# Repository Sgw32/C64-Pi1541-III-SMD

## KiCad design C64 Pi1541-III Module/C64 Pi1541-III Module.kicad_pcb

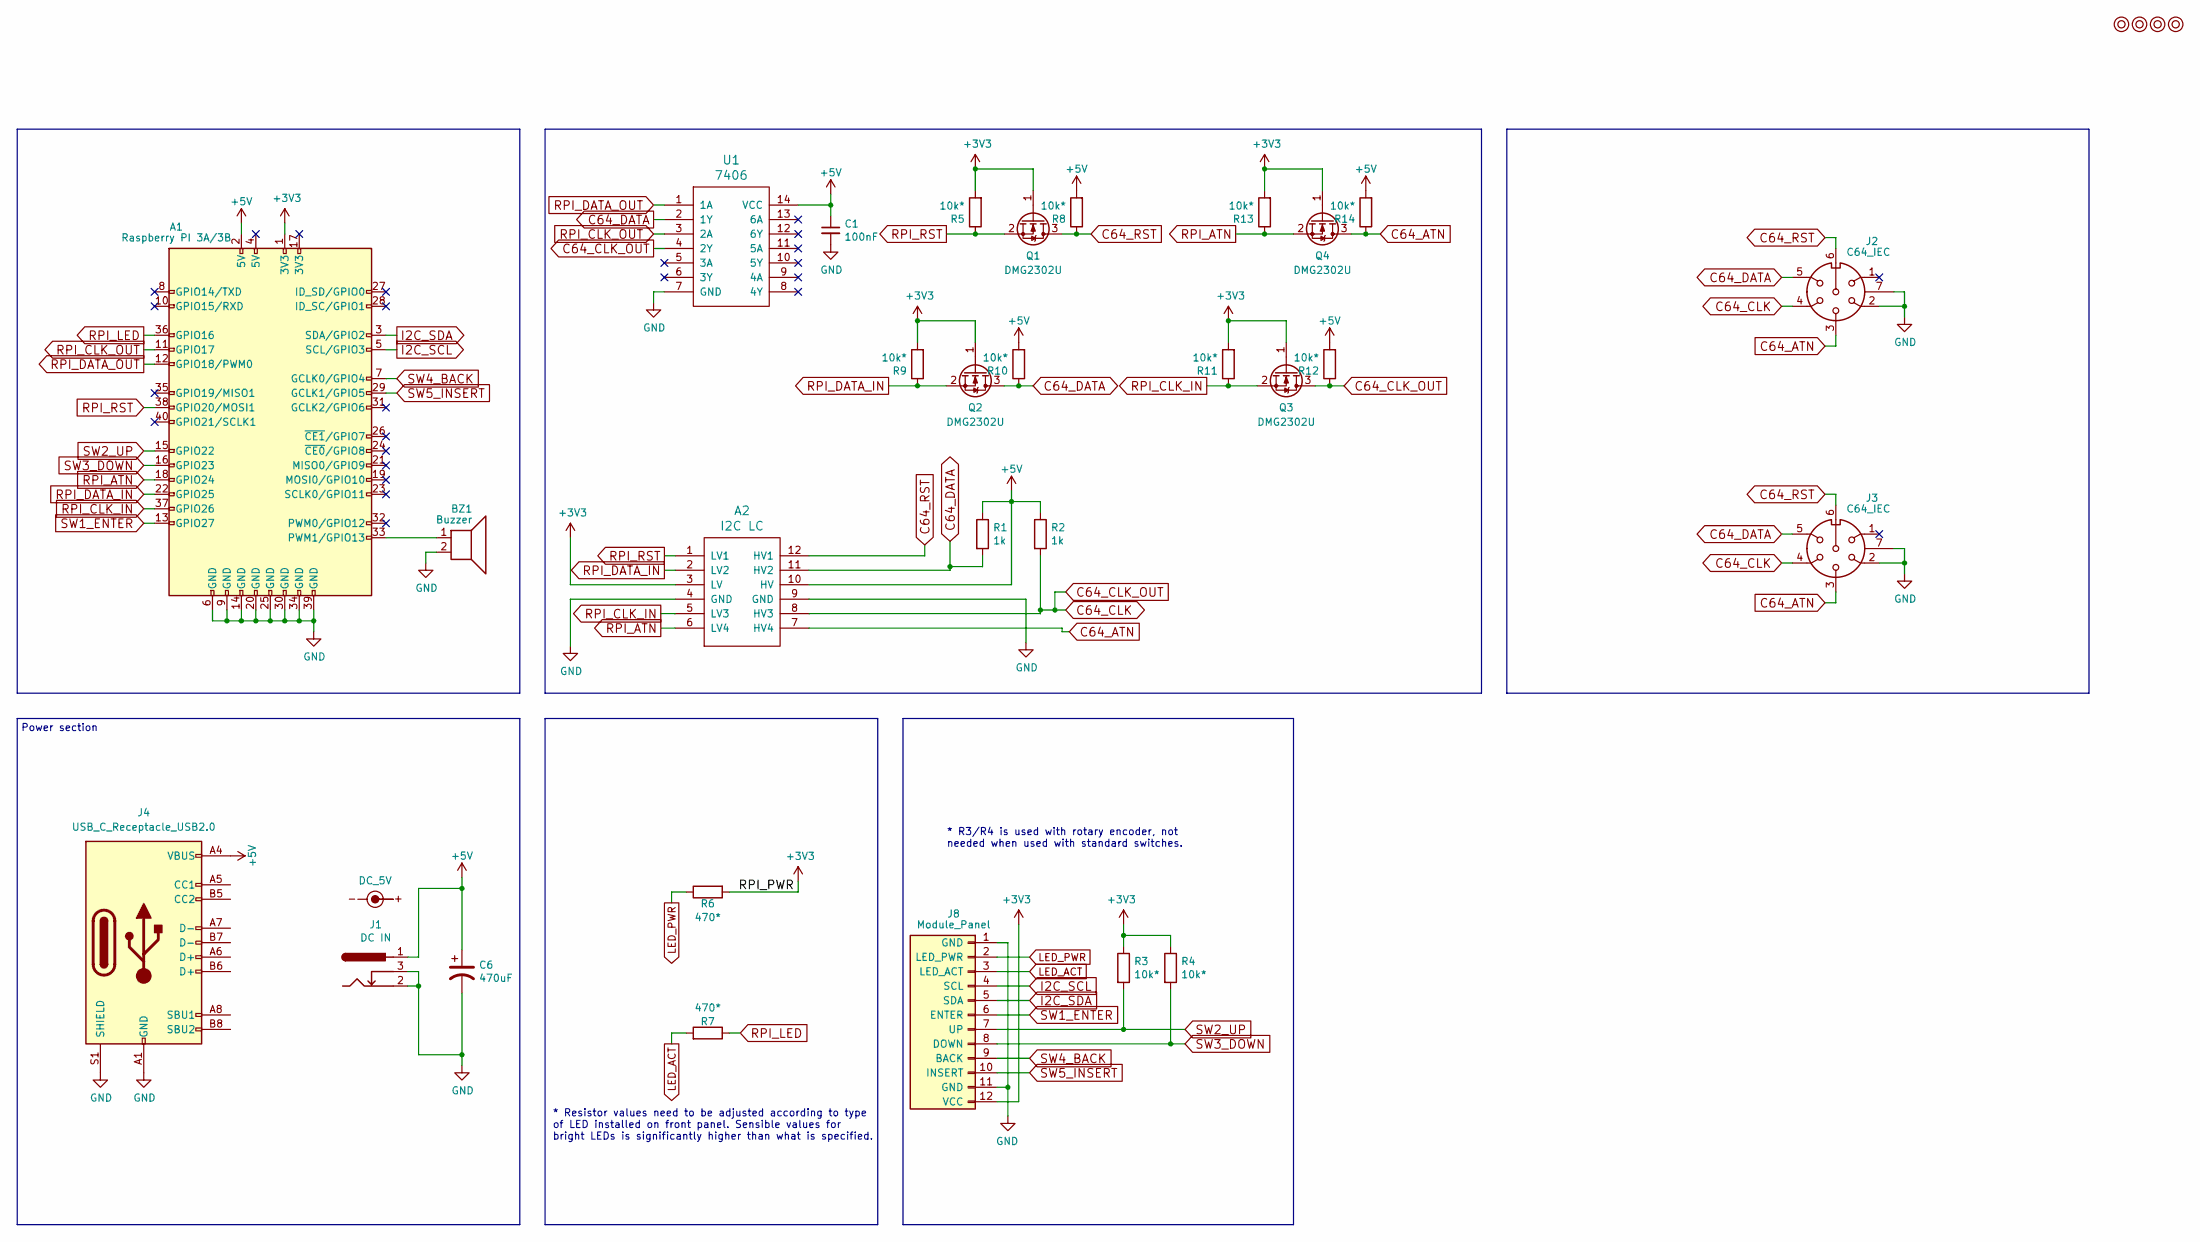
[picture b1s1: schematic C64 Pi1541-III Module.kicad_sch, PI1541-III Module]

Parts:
A1: Raspberry PI 3A/3B; Raspberry_Pi_3B_Socketed_THT_FaceDown_MountingHoles
A2: I2C LC; 4CH_I2C_Level_Converter
BZ1: Buzzer; Buzzer_12x9.5RM7.6
C1: 100nF; C_0805_2012Metric
C6: 470uF; CP_Elec_10x7.7
J1: DC IN; BarrelJack_CLIFF_FC681465S_SMT_Horizontal
J2, J3: C64_IEC; DIN6_IEC
J4: USB_C_Receptacle_USB2.0; USB_C_Receptacle_XKB_U262-16XN-4BVC11
J8: Module_Panel
M1, M2, M3, M4: Mounting; M3
Q1, Q2, Q3, Q4: DMG2302U; SOT-23
R1, R2: 1k; R_0805_2012Metric
R3, R4, R5, R8, R9, R10, R11, R12, R13, R14: 10k*; R_0805_2012Metric
R6, R7: 470*; R_0805_2012Metric
SYM1: DC_5V; PWR_Specification
U1: 7406; SO-14_3.9x8.65mm_P1.27mm

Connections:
+3V3: A1.1 (3V3), A2.3 (LV), J8.12 (VCC), Q1.1 (G), Q2.1 (G), Q3.1 (G), Q4.1 (G), R3.1, R4.1, R5.2, R6.2, R9.2, R11.2, R13.2
+5V: A1.2 (5V), A2.10 (HV), C1.1, C6.1, J1.1, J4.A4 (VBUS), J4.A9 (VBUS), J4.B4 (VBUS), J4.B9 (VBUS), R1.1, R2.1, R8.2, R10.2, R12.2, R14.2, U1.14 (VCC)
C64_ATN: A2.7 (HV4), J2.3, J3.3, Q4.3 (D), R14.1
C64_CLK: A2.8 (HV3), J2.4, J3.4, Q3.3 (D), R2.2, R12.1, U1.4 (2Y)
C64_DATA: A2.11 (HV2), J2.5, J3.5, Q2.3 (D), R1.2, R10.1, U1.2 (1Y)
C64_RST: A2.12 (HV1), J2.6, J3.6, Q1.3 (D), R8.1
GND: A1.6 (GND), A1.9 (GND), A1.14 (GND), A1.20 (GND), A1.25 (GND), A1.30 (GND), A1.34 (GND), A1.39 (GND), A2.4 (GND), A2.9 (GND), BZ1.2, C1.2, C6.2, J1.2, J1.3, J2.2, J2.7, J3.2, J3.7, J4.A1 (GND), J4.A12 (GND), J4.B1 (GND), J4.B12 (GND), J4.S1 (SHIELD), J8.1 (GND), J8.11 (GND), U1.7 (GND)
I2C_SCL: A1.5 (SCL/GPIO3), J8.4 (SCL)
I2C_SDA: A1.3 (SDA/GPIO2), J8.5 (SDA)
LED_ACT: J8.3 (LED_ACT), R7.2
LED_PWR: J8.2 (LED_PWR), R6.1
unnamed: A1.33 (PWM1/GPIO13), BZ1.1
RPI_ATN: A1.18 (GPIO24), A2.6 (LV4), Q4.2 (S), R13.1
RPI_CLK_IN: A1.37 (GPIO26), A2.5 (LV3), Q3.2 (S), R11.1
RPI_CLK_OUT: A1.11 (GPIO17), U1.3 (2A)
RPI_DATA_IN: A1.22 (GPIO25), A2.2 (LV2), Q2.2 (S), R9.1
RPI_DATA_OUT: A1.12 (GPIO18/PWM0), U1.1 (1A)
RPI_LED: A1.36 (GPIO16), R7.1
RPI_RST: A1.38 (GPIO20/MOSI1), A2.1 (LV1), Q1.2 (S), R5.1
SW1_ENTER: A1.13 (GPIO27), J8.6 (ENTER)
SW2_UP: A1.15 (GPIO22), J8.7 (UP), R3.2
SW3_DOWN: A1.16 (GPIO23), J8.8 (DOWN), R4.2
SW4_BACK: A1.7 (GCLK0/GPIO4), J8.9 (BACK)
SW5_INSERT: A1.29 (GCLK1/GPIO5), J8.10 (INSERT)

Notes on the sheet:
Power section
* R3/R4 is used with rotary encoder, not needed when used with standard switches.
* Resistor values need to be adjusted according to type of LED installed on front panel. Sensible values for bright LEDs is significantly higher than what is specified.

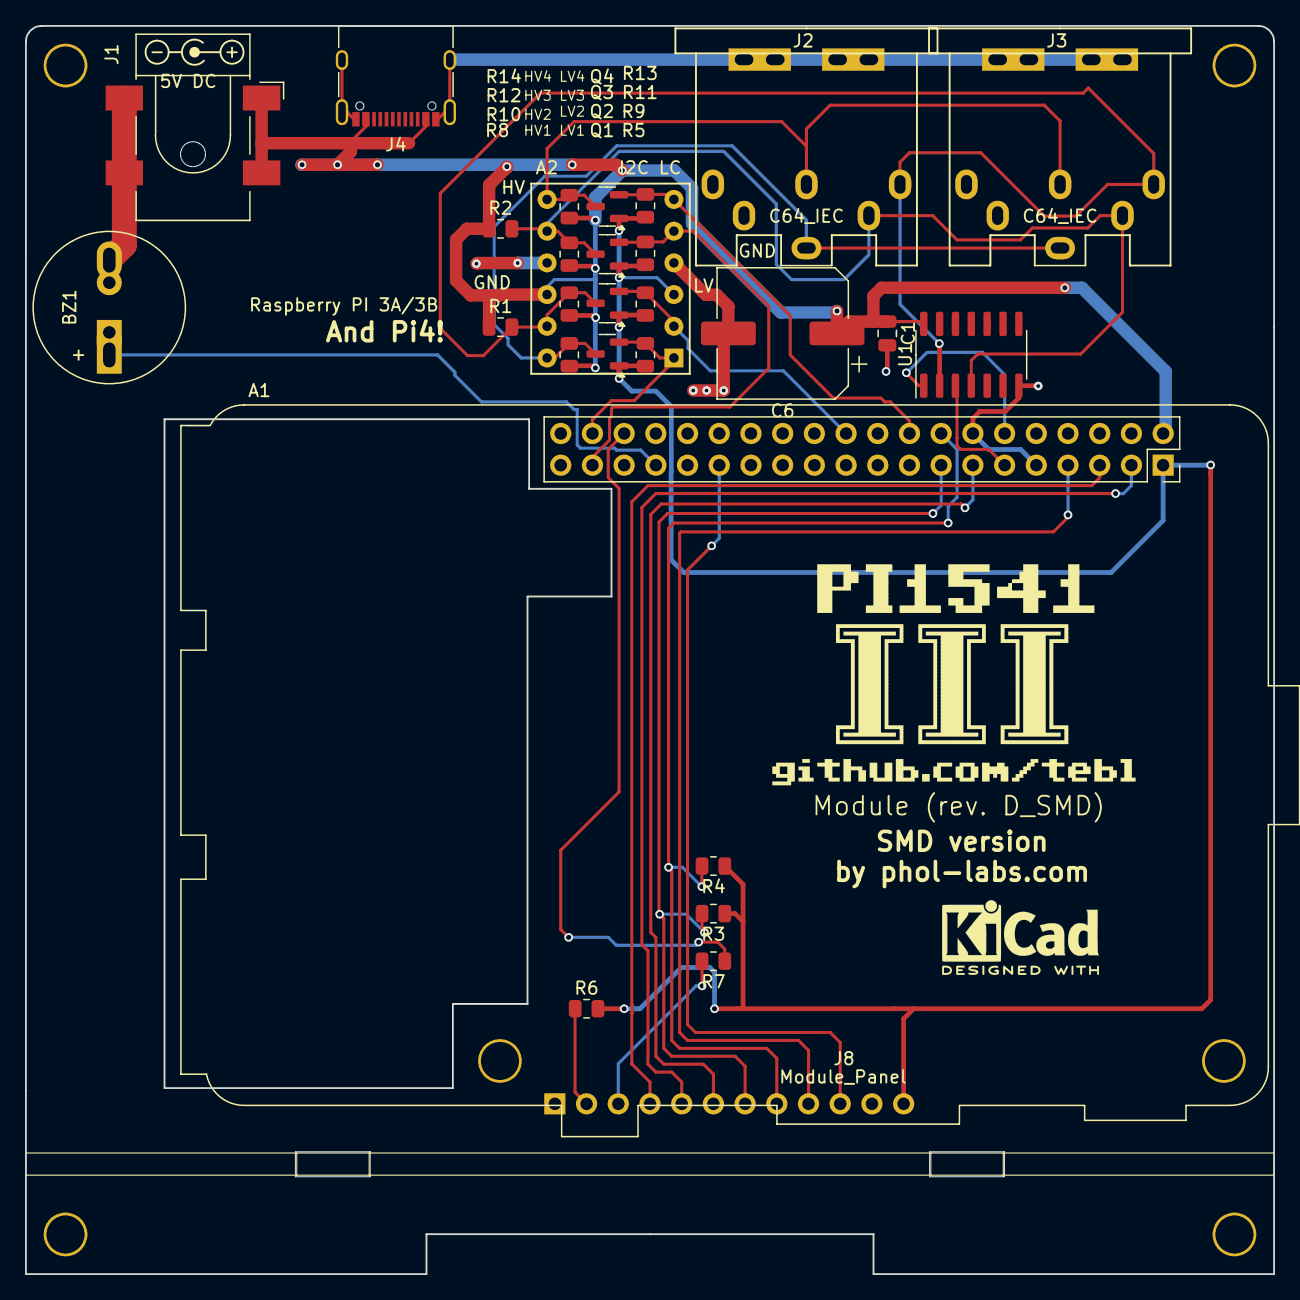
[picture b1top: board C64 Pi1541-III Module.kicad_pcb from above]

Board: 2 copper layers, 100.0 x 100.0 mm, 35 parts (1 on the bottom side), 24 nets.

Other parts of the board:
Pi1541-drive: Pi1541-drive

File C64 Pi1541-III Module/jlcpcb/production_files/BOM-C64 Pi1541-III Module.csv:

Comment,Designator,Footprint,LCSC,Quantity
DC IN,J1,BarrelJack_CLIFF_FC681465S_SMT_Horizontal,C114916,1
Raspberry PI 3A/3B,A1,Raspberry_Pi_3B_Socketed_THT_FaceDown_MountingHoles,C132132,1
USB_C_Receptacle_USB2.0,J4,USB_C_Receptacle_XKB_U262-16XN-4BVC11,C165948,1
10k*,"R10,R11,R12,R13,R14,R3,R4,R5,R8,R9",R_0805_2012Metric,C17414,10
1k,"R1,R2",R_0805_2012Metric,C17513,2
470*,"R6,R7",R_0805_2012Metric,C17710,2
Buzzer,BZ1,Buzzer_12x9.5RM7.6,C252916,1
DMG2302U,"Q1,Q2,Q3,Q4",SOT-23,C427390,4
100nF,C1,C_0805_2012Metric,C49678,1
7406,U1,SO-14_3.9x8.65mm_P1.27mm,C5592,1
470uF,C6,CP_Elec_10x7.7,C88671,1

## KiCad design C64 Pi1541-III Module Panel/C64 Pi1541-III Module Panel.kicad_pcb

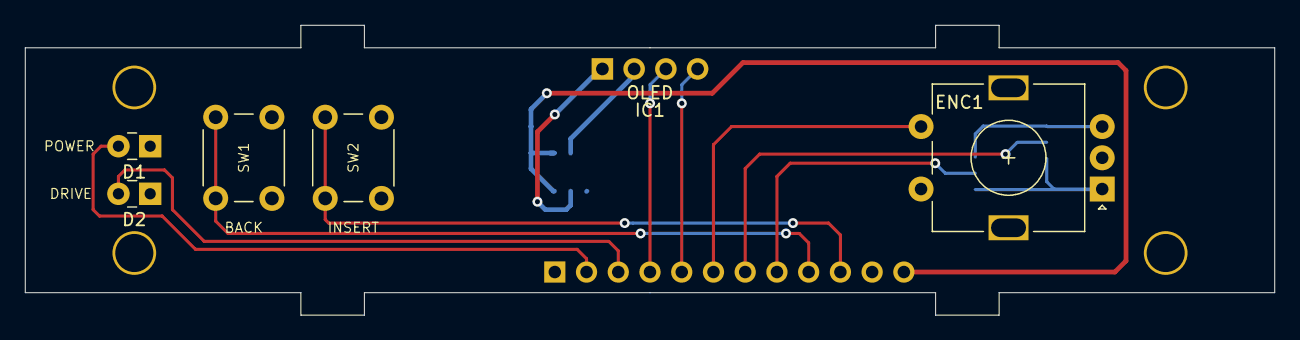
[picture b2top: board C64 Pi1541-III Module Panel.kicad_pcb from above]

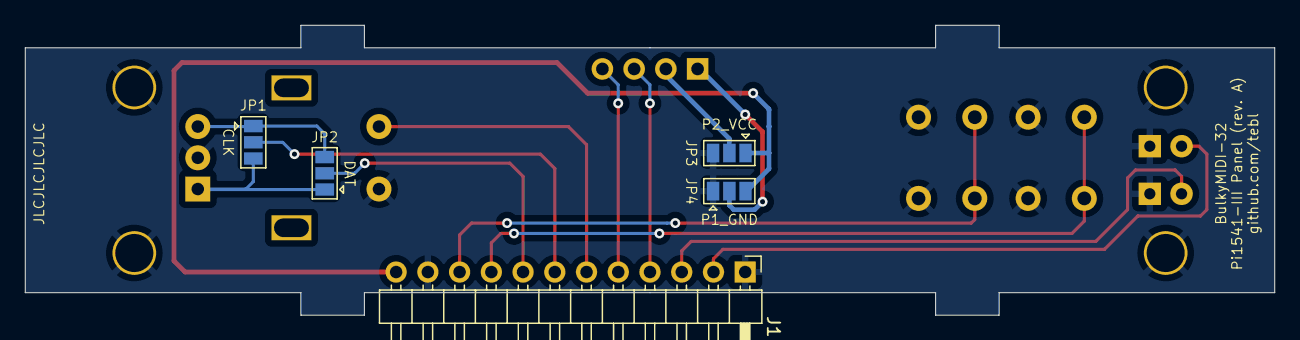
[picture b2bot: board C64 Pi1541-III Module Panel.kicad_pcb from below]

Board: 2 copper layers, 100.0 x 23.2 mm, 15 parts (5 on the bottom side), 15 nets.

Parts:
D1: POWER; LED_Rectangular_W3.0mm_H2.0mm
D2: DRIVE; LED_Rectangular_W3.0mm_H2.0mm
ENC1: Rotary_Encoder_Switch; RotaryEncoder_Alps_EC11E-Switch_Vertical_H20mm
IC1: OLED; 1.3_I2C_OLED_No_mounting
J1: Module Panel; PinHeader_1x12_P2.54mm_Horizontal
JP1: CLK; SolderJumper-3_P1.3mm_Open_Pad1.0x1.5mm
JP2: DAT; SolderJumper-3_P1.3mm_Open_Pad1.0x1.5mm
JP3: P1_GND; SolderJumper-3_P1.3mm_Open_Pad1.0x1.5mm
JP4: P2_VCC; SolderJumper-3_P1.3mm_Open_Pad1.0x1.5mm
M1, M2, M3, M4: Mounting_Pin; M3_pin
SW1: BACK; SW_PUSH_6mm
SW2: INSERT; SW_PUSH_6mm

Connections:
/A: ENC1.A, JP1.3, JP2.1
/B: ENC1.B, JP1.1, JP2.3
GND: D1.1, D2.1, ENC1.C, ENC1.S2, J1.1, J1.11, JP3.1, JP4.3, M1.1, M2.1, M3.1, M4.1, SW1.2, SW2.2
I2C_SCL: IC1.3, J1.4
I2C_SDA: IC1.4, J1.5
LED_ACT: D2.2, J1.3
LED_PWR: D1.2, J1.2
unnamed: IC1.1, JP3.2
unnamed: IC1.2, JP4.2
SW_BACK: J1.9, SW1.1
SW_DOWN: J1.8, JP2.2
SW_ENTER: ENC1.S1, J1.6
SW_INSERT: J1.10, SW2.1
SW_UP: J1.7, JP1.2
VCC: J1.12, JP3.3, JP4.1

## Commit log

2025-03-15 SMD option for Pi1541-III
2025-07-16 Version with more SMD comp - finished, there will be a new revision
